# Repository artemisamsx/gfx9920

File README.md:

# Artemisa MSX - GFX9920 Graphics Card

This repository contains the KiCad project files for the GFX9920 graphics card.

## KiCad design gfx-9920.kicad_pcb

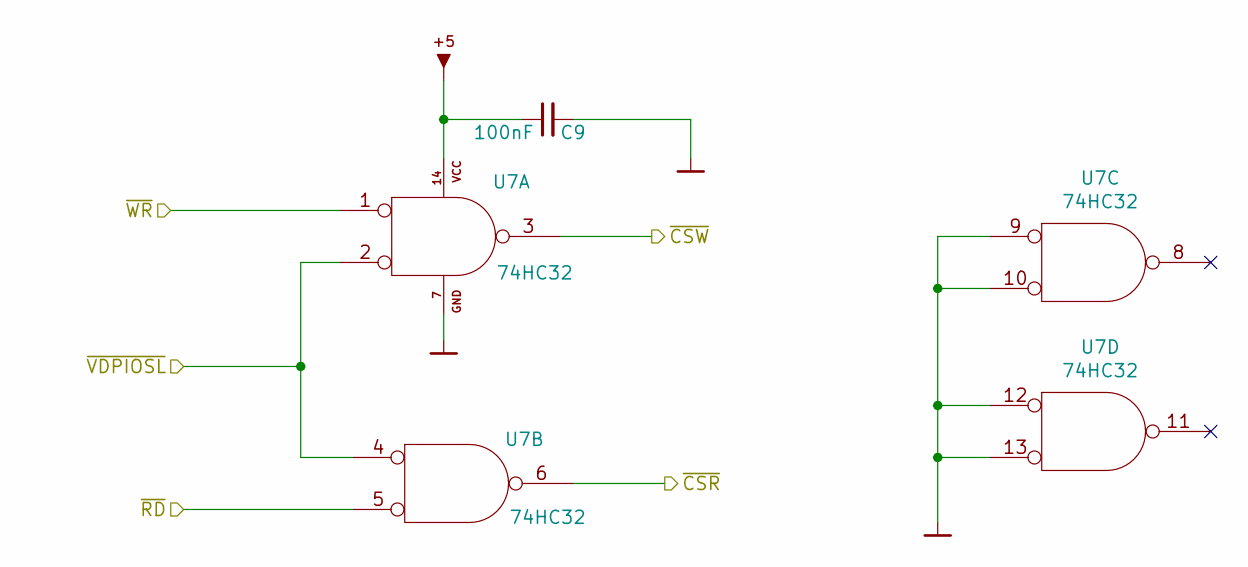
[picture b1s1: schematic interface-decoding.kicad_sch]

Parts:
C9: 100nF; Disc_capacitor
U7: 74HC32; DIP-14_300

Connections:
/Card connector & power/BUSDIR: U7.6; also elsewhere on the board
/Card connector & power/~RD: U7.5; also elsewhere on the board
/Card connector & power/~VDPIOSL: U7.2, U7.4; also elsewhere on the board
/Card connector & power/~WR: U7.1; also elsewhere on the board
/Interface Decoding Logic/~CSW: U7.3; also elsewhere on the board
GND: C9.2, U7.7 (GND), U7.9, U7.10, U7.12, U7.13; also elsewhere on the board
VCC: C9.1, U7.14 (VCC); also elsewhere on the board

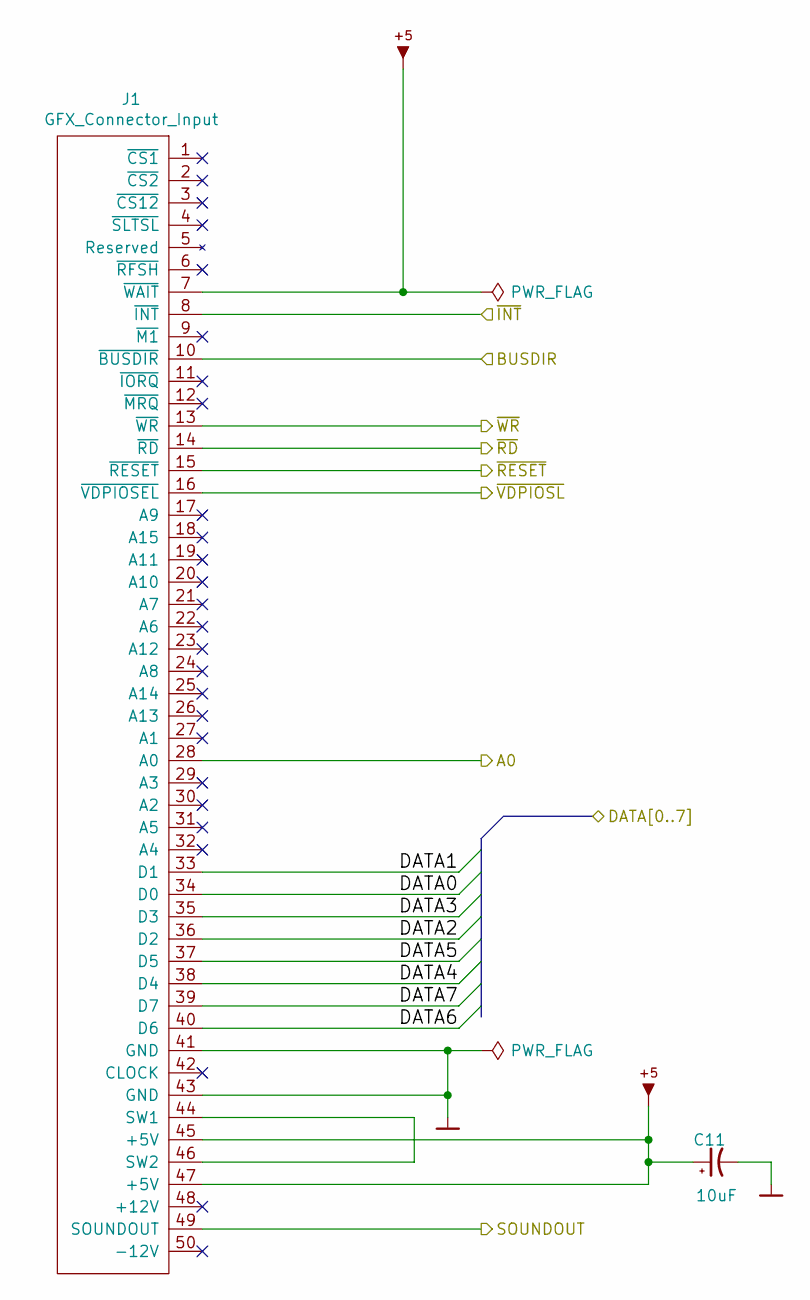
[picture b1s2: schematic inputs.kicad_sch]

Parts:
C11: 10uF; Radial_capacitor
J1: GFX_Connector_Input; GFX_conn

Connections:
/Card connector & power/A0: J1.28 (A0); also elsewhere on the board
/Card connector & power/BUSDIR: J1.10 (~BUSDIR); also elsewhere on the board
/Card connector & power/SOUNDOUT: J1.49 (SOUNDOUT); also elsewhere on the board
/Card connector & power/~INT: J1.8 (~INT); also elsewhere on the board
/Card connector & power/~RD: J1.14 (~RD); also elsewhere on the board
/Card connector & power/~RESET: J1.15 (~RESET); also elsewhere on the board
/Card connector & power/~VDPIOSL: J1.16 (~VDPIOSEL); also elsewhere on the board
/Card connector & power/~WR: J1.13 (~WR); also elsewhere on the board
/DATA0: J1.34 (D0); also elsewhere on the board
/DATA1: J1.33 (D1); also elsewhere on the board
/DATA2: J1.36 (D2); also elsewhere on the board
/DATA3: J1.35 (D3); also elsewhere on the board
/DATA4: J1.38 (D4); also elsewhere on the board
/DATA5: J1.37 (D5); also elsewhere on the board
/DATA6: J1.40 (D6); also elsewhere on the board
/DATA7: J1.39 (D7); also elsewhere on the board
GND: C11.2, J1.41 (GND), J1.43 (GND); also elsewhere on the board
unnamed: J1.44 (SW1), J1.46 (SW2)
VCC: C11.1, J1.7 (~WAIT), J1.45 (+5V), J1.47 (+5V); also elsewhere on the board

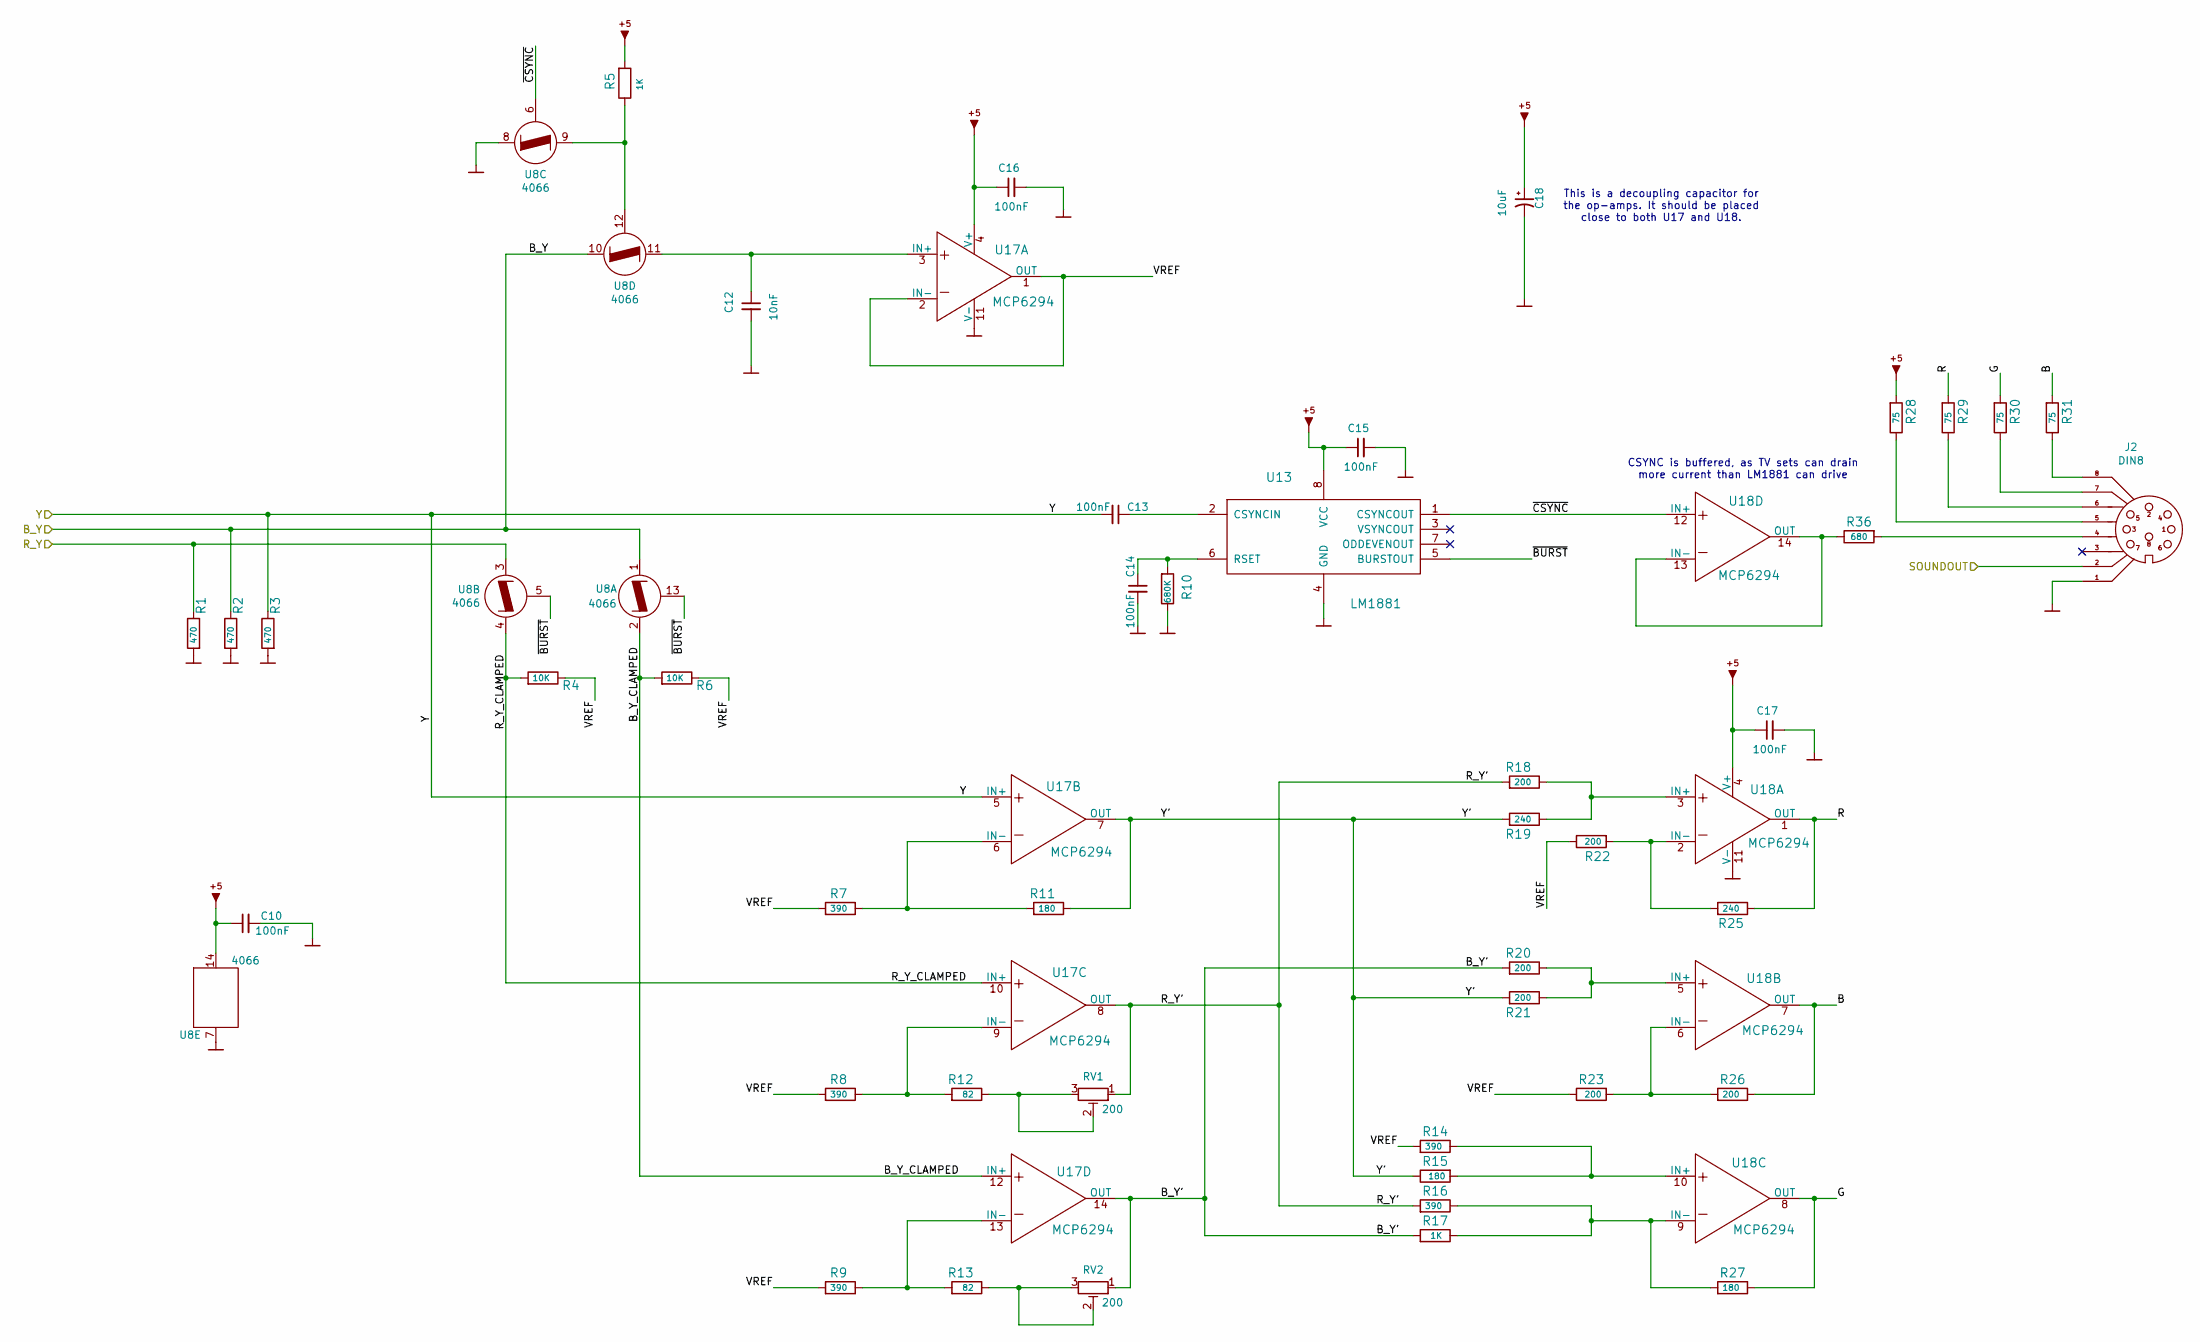
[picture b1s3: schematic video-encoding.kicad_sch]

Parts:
C10, C13, C14, C15, C16, C17: 100nF; Disc_capacitor
C12: 10nF; C_Rect_L7.0mm_W3.5mm_P2.50mm_P5.00mm
C18: 10uF; Radial_capacitor
J2: DIN8
R1, R2, R3: 470; Axial_resistor
R4, R6: 10K; Axial_resistor
R5, R17: 1K; Axial_resistor
R7, R8, R9, R14, R16: 390; Axial_resistor
R10: 680K; Axial_resistor
R11, R15, R27: 180; Axial_resistor
R12, R13: 82; Axial_resistor
R18, R20, R21, R22, R23, R26: 200; Axial_resistor
R19, R25: 240; Axial_resistor
R28, R29, R30, R31: 75; Axial_resistor
R36: 680; Axial_resistor
RV1, RV2: 200; Potentiometer_Bourns_3296W_Vertical
U8: 4066; DIP-14_300
U13: LM1881; DIP-8_300
U17, U18: MCP6294; DIP-14_300

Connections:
/Card connector & power/SOUNDOUT: J2.2; also elsewhere on the board
/Video Display Processor/R_Y: R1.1, U8.3; also elsewhere on the board
/Video Encoding/B: R26.1, R31.2, U18.7 (OUT)
/Video Encoding/B_Y: R2.1, U8.1, U8.10; also elsewhere on the board
/Video Encoding/B_Y': R17.2, R20.2, RV2.1, U17.14 (OUT)
/Video Encoding/B_Y_CLAMPED: R6.2, U8.2, U17.12 (IN+)
/Video Encoding/G: R27.1, R30.2, U18.8 (OUT)
/Video Encoding/R: R25.1, R29.2, U18.1 (OUT)
/Video Encoding/R_Y': R16.2, R18.2, RV1.1, U17.8 (OUT)
/Video Encoding/R_Y_CLAMPED: R4.2, U8.4, U17.10 (IN+)
/Video Encoding/VREF: R4.1, R6.1, R7.2, R8.2, R9.2, R14.2, R22.1, R23.1, U17.1 (OUT), U17.2 (IN-)
/Video Encoding/Y: C13.2, R3.1, U17.5 (IN+); also elsewhere on the board
/Video Encoding/Y': R11.1, R15.1, R19.2, R21.2, U17.7 (OUT)
/Video Encoding/~BURST: U8.5, U8.13, U13.5 (BURSTOUT)
/Video Encoding/~CSYNC: U8.6, U13.1 (CSYNCOUT), U18.12 (IN+)
GND: C10.2, C12.2, C14.2, C15.2, C16.2, C17.2, C18.2, J2.1, R1.2, R2.2, R3.2, R10.1, U8.7, U8.8, U13.4 (GND), U17.11 (V-), U18.11 (V-); also elsewhere on the board
unnamed: J2.4, R36.2
unnamed: J2.5, R28.1
unnamed: J2.6, R29.1
unnamed: J2.7, R30.1
unnamed: J2.8, R31.1
unnamed: R5.1, U8.9, U8.12
unnamed: R12.1, RV1.2, RV1.3
unnamed: R13.1, RV2.2, RV2.3
unnamed: C13.1, U13.2 (CSYNCIN)
unnamed: C14.1, R10.2, U13.6 (RSET)
unnamed: C12.1, U8.11, U17.3 (IN+)
unnamed: R7.1, R11.2, U17.6 (IN-)
unnamed: R8.1, R12.2, U17.9 (IN-)
unnamed: R9.1, R13.2, U17.13 (IN-)
unnamed: R18.1, R19.1, U18.3 (IN+)
unnamed: R22.2, R25.2, U18.2 (IN-)
unnamed: R20.1, R21.1, U18.5 (IN+)
unnamed: R23.2, R26.2, U18.6 (IN-)
unnamed: R14.1, R15.2, U18.10 (IN+)
unnamed: R16.1, R17.1, R27.2, U18.9 (IN-)
unnamed: R36.1, U18.13 (IN-), U18.14 (OUT)
VCC: C10.1, C15.1, C16.1, C17.1, C18.1, R5.2, R28.2, U8.14 (VCC_14), U13.8 (VCC), U17.4 (V+), U18.4 (V+); also elsewhere on the board

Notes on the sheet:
CSYNC is buffered, as TV sets can drain more current than LM1881 can drive
This is a decoupling capacitor for the op-amps. It should be placed close to both U17 and U18.

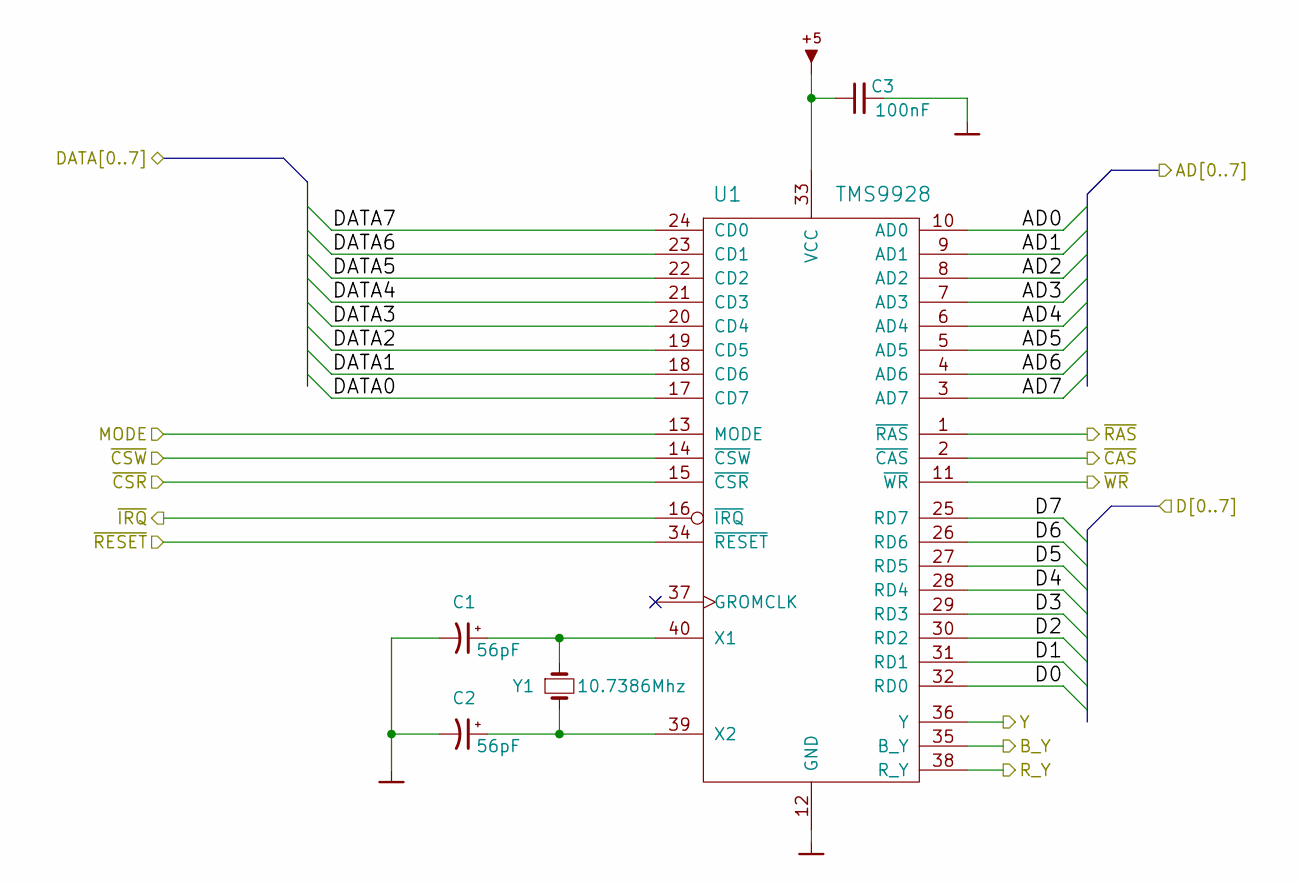
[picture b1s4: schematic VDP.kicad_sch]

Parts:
C1, C2: 56pF; Disc_capacitor
C3: 100nF; Disc_capacitor
U1: TMS9928; DIP-40_600
Y1: 10.7386Mhz; Crystal

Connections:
/AD0: U1.10 (AD0); also elsewhere on the board
/AD1: U1.9 (AD1); also elsewhere on the board
/AD2: U1.8 (AD2); also elsewhere on the board
/AD3: U1.7 (AD3); also elsewhere on the board
/AD4: U1.6 (AD4); also elsewhere on the board
/AD5: U1.5 (AD5); also elsewhere on the board
/AD6: U1.4 (AD6); also elsewhere on the board
/AD7: U1.3 (AD7); also elsewhere on the board
/Card connector & power/A0: U1.13 (MODE); also elsewhere on the board
/Card connector & power/BUSDIR: U1.15 (~CSR); also elsewhere on the board
/Card connector & power/~INT: U1.16 (~IRQ); also elsewhere on the board
/Card connector & power/~RESET: U1.34 (~RESET); also elsewhere on the board
/D0: U1.32 (RD0); also elsewhere on the board
/D1: U1.31 (RD1); also elsewhere on the board
/D2: U1.30 (RD2); also elsewhere on the board
/D3: U1.29 (RD3); also elsewhere on the board
/D4: U1.28 (RD4); also elsewhere on the board
/D5: U1.27 (RD5); also elsewhere on the board
/D6: U1.26 (RD6); also elsewhere on the board
/D7: U1.25 (RD7); also elsewhere on the board
/DATA0: U1.17 (CD7); also elsewhere on the board
/DATA1: U1.18 (CD6); also elsewhere on the board
/DATA2: U1.19 (CD5); also elsewhere on the board
/DATA3: U1.20 (CD4); also elsewhere on the board
/DATA4: U1.21 (CD3); also elsewhere on the board
/DATA5: U1.22 (CD2); also elsewhere on the board
/DATA6: U1.23 (CD1); also elsewhere on the board
/DATA7: U1.24 (CD0); also elsewhere on the board
/Interface Decoding Logic/~CSW: U1.14 (~CSW); also elsewhere on the board
/VRAM Decoding Logic/~CAS: U1.2 (~CAS); also elsewhere on the board
/VRAM Decoding Logic/~RAS: U1.1 (~RAS); also elsewhere on the board
/VRAM Decoding Logic/~WR: U1.11 (~WR); also elsewhere on the board
/Video Display Processor/R_Y: U1.38 (R_Y); also elsewhere on the board
/Video Encoding/B_Y: U1.35 (B_Y); also elsewhere on the board
/Video Encoding/Y: U1.36 (Y); also elsewhere on the board
GND: C1.2, C2.2, C3.2, U1.12 (GND); also elsewhere on the board
unnamed: C1.1, U1.40 (X1), Y1.1
unnamed: C2.1, U1.39 (X2), Y1.2
VCC: C3.1, U1.33 (VCC); also elsewhere on the board

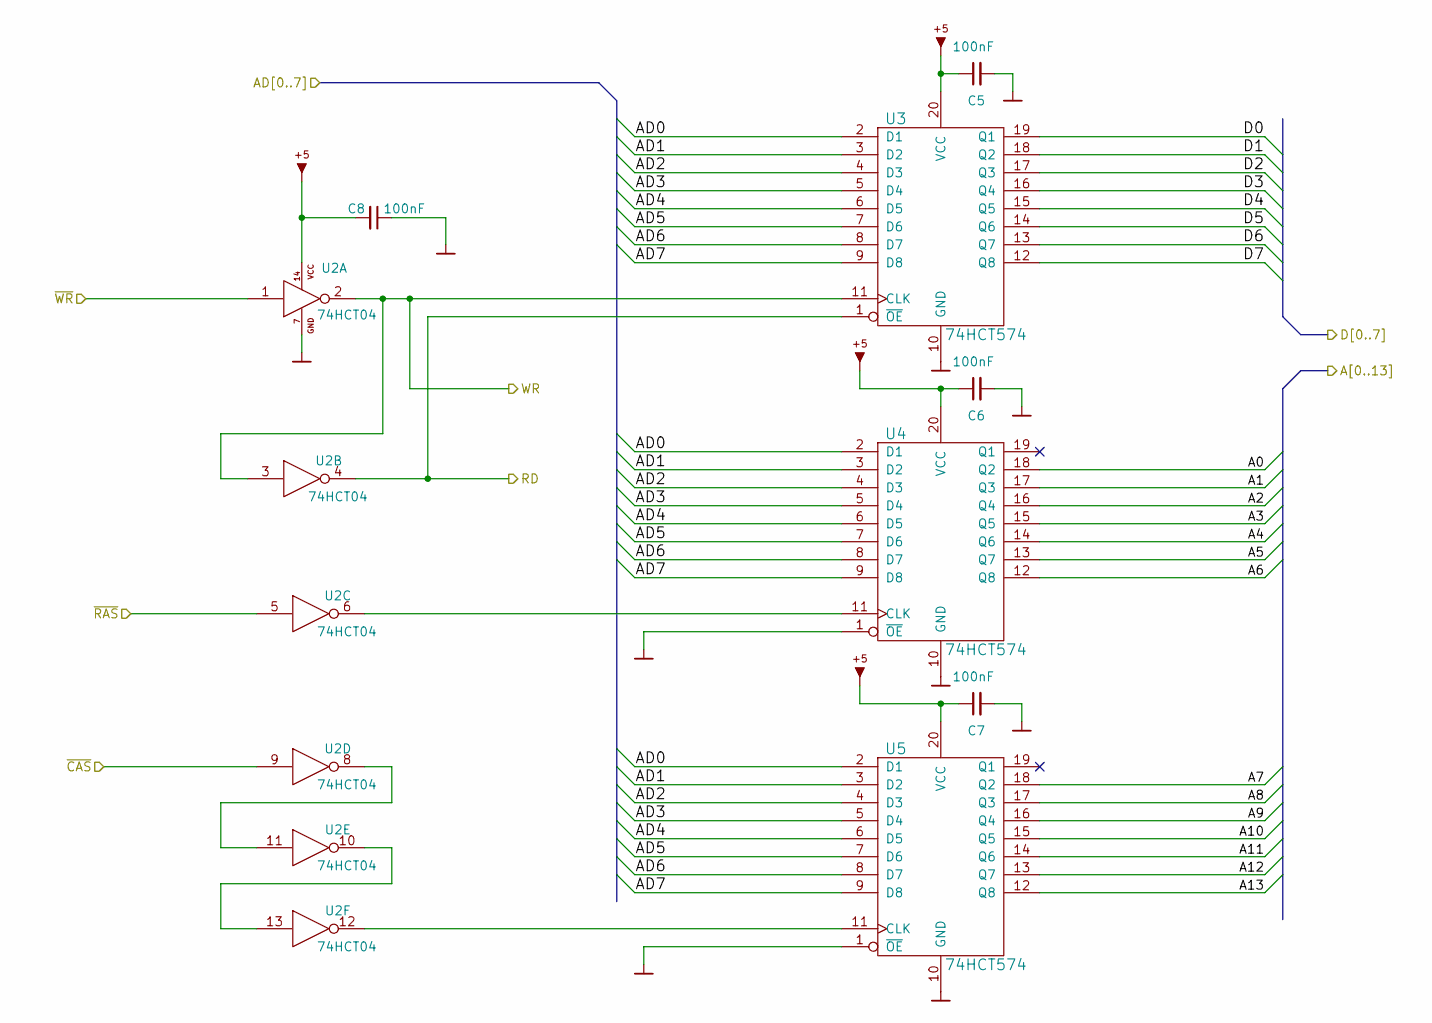
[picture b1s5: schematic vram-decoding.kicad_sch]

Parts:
C5, C6, C7, C8: 100nF; Disc_capacitor
U2: 74HCT04; DIP-14_300
U3, U4, U5: 74HCT574; DIP-20_300

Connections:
/A0: U4.18 (Q2); also elsewhere on the board
/A1: U4.17 (Q3); also elsewhere on the board
/A2: U4.16 (Q4); also elsewhere on the board
/A3: U4.15 (Q5); also elsewhere on the board
/A4: U4.14 (Q6); also elsewhere on the board
/A5: U4.13 (Q7); also elsewhere on the board
/A6: U4.12 (Q8); also elsewhere on the board
/A7: U5.18 (Q2); also elsewhere on the board
/A8: U5.17 (Q3); also elsewhere on the board
/A9: U5.16 (Q4); also elsewhere on the board
/A10: U5.15 (Q5); also elsewhere on the board
/A11: U5.14 (Q6); also elsewhere on the board
/A12: U5.13 (Q7); also elsewhere on the board
/A13: U5.12 (Q8); also elsewhere on the board
/AD0: U3.2 (D1), U4.2 (D1), U5.2 (D1); also elsewhere on the board
/AD1: U3.3 (D2), U4.3 (D2), U5.3 (D2); also elsewhere on the board
/AD2: U3.4 (D3), U4.4 (D3), U5.4 (D3); also elsewhere on the board
/AD3: U3.5 (D4), U4.5 (D4), U5.5 (D4); also elsewhere on the board
/AD4: U3.6 (D5), U4.6 (D5), U5.6 (D5); also elsewhere on the board
/AD5: U3.7 (D6), U4.7 (D6), U5.7 (D6); also elsewhere on the board
/AD6: U3.8 (D7), U4.8 (D7), U5.8 (D7); also elsewhere on the board
/AD7: U3.9 (D8), U4.9 (D8), U5.9 (D8); also elsewhere on the board
/D0: U3.19 (Q1); also elsewhere on the board
/D1: U3.18 (Q2); also elsewhere on the board
/D2: U3.17 (Q3); also elsewhere on the board
/D3: U3.16 (Q4); also elsewhere on the board
/D4: U3.15 (Q5); also elsewhere on the board
/D5: U3.14 (Q6); also elsewhere on the board
/D6: U3.13 (Q7); also elsewhere on the board
/D7: U3.12 (Q8); also elsewhere on the board
/VRAM Decoding Logic/RD: U2.4, U3.1 (~OE); also elsewhere on the board
/VRAM Decoding Logic/WR: U2.2, U2.3, U3.11 (CLK); also elsewhere on the board
/VRAM Decoding Logic/~CAS: U2.9; also elsewhere on the board
/VRAM Decoding Logic/~RAS: U2.5; also elsewhere on the board
/VRAM Decoding Logic/~WR: U2.1; also elsewhere on the board
GND: C5.2, C6.2, C7.2, C8.1, U2.7 (GND), U3.10 (GND), U4.1 (~OE), U4.10 (GND), U5.1 (~OE), U5.10 (GND); also elsewhere on the board
unnamed: U2.10, U2.13
unnamed: U2.8, U2.11
unnamed: U2.6, U4.11 (CLK)
unnamed: U2.12, U5.11 (CLK)
VCC: C5.1, C6.1, C7.1, C8.2, U2.14 (VCC), U3.20 (VCC), U4.20 (VCC), U5.20 (VCC); also elsewhere on the board

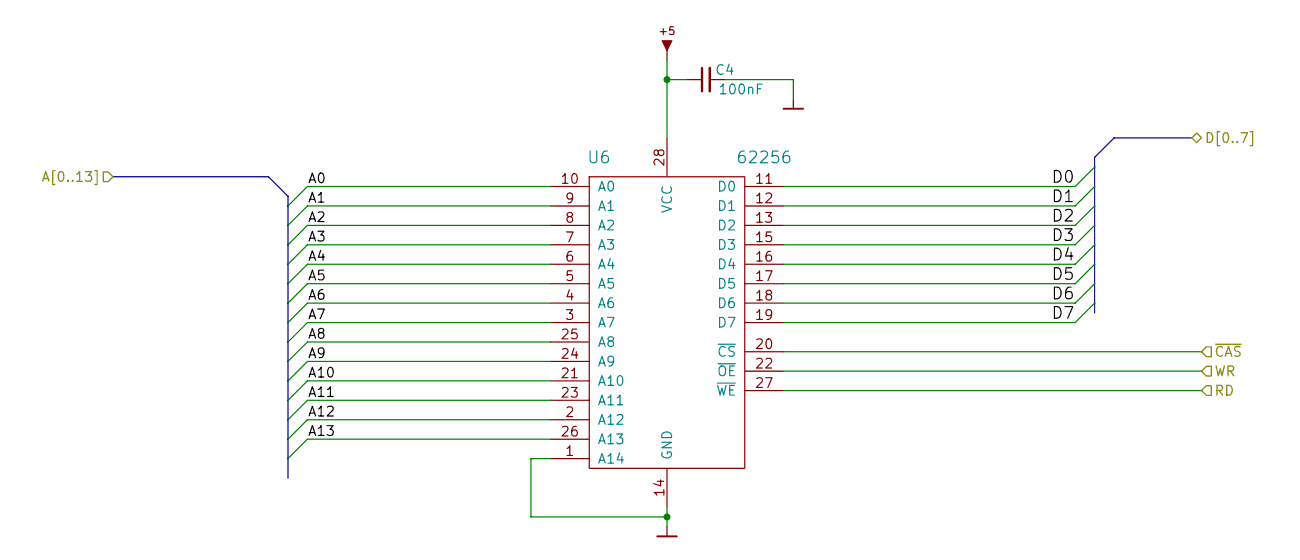
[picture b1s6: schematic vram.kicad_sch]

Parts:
C4: 100nF; Disc_capacitor
U6: 62256; DIP-28_600

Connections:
/A0: U6.10 (A0); also elsewhere on the board
/A1: U6.9 (A1); also elsewhere on the board
/A2: U6.8 (A2); also elsewhere on the board
/A3: U6.7 (A3); also elsewhere on the board
/A4: U6.6 (A4); also elsewhere on the board
/A5: U6.5 (A5); also elsewhere on the board
/A6: U6.4 (A6); also elsewhere on the board
/A7: U6.3 (A7); also elsewhere on the board
/A8: U6.25 (A8); also elsewhere on the board
/A9: U6.24 (A9); also elsewhere on the board
/A10: U6.21 (A10); also elsewhere on the board
/A11: U6.23 (A11); also elsewhere on the board
/A12: U6.2 (A12); also elsewhere on the board
/A13: U6.26 (A13); also elsewhere on the board
/D0: U6.11 (D0); also elsewhere on the board
/D1: U6.12 (D1); also elsewhere on the board
/D2: U6.13 (D2); also elsewhere on the board
/D3: U6.15 (D3); also elsewhere on the board
/D4: U6.16 (D4); also elsewhere on the board
/D5: U6.17 (D5); also elsewhere on the board
/D6: U6.18 (D6); also elsewhere on the board
/D7: U6.19 (D7); also elsewhere on the board
/VRAM Decoding Logic/RD: U6.27 (~WE); also elsewhere on the board
/VRAM Decoding Logic/WR: U6.22 (~OE); also elsewhere on the board
/VRAM Decoding Logic/~CAS: U6.20 (~CS); also elsewhere on the board
GND: C4.2, U6.1 (A14), U6.14 (GND); also elsewhere on the board
VCC: C4.1, U6.28 (VCC); also elsewhere on the board

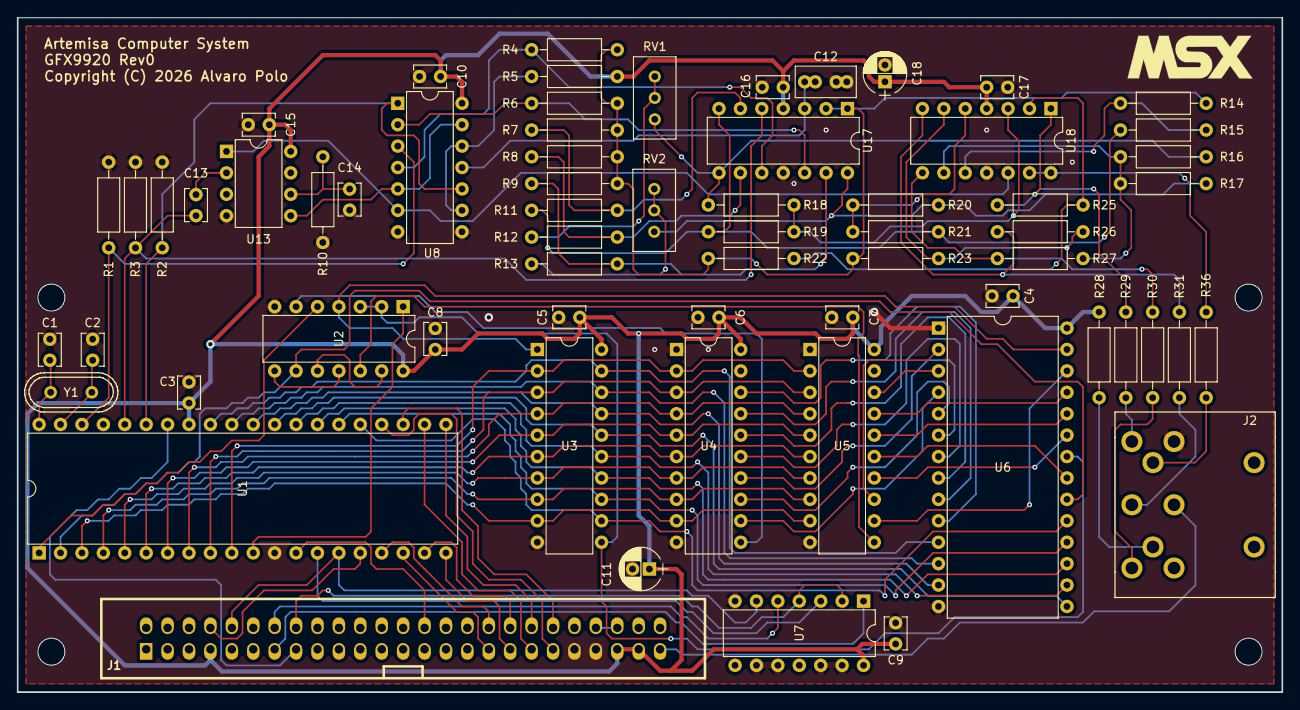
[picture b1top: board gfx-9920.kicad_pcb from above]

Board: 2 copper layers, 150.0 x 80.0 mm, 65 parts (0 on the bottom side), 96 nets.

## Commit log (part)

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2019-09-14 [gfx9920] Scaffold KiCAD project as a clone of GFX9918
2019-09-30 [WIP] GFX9920 stuff
2019-09-30 [gfx9920] Use 9928 instead of 9918
2019-09-30 [gfx9920] Introduce LM1881
2020-05-31 [GFX9920] Include working output line for /CSYNC
2020-05-31 [gfx9920] Remove extra resistors for component video lines
2020-05-31 [GFX9920] Complete the first proposal of encoder circuit
2020-06-03 [gfx9920] Move G encoding resistors to clarify
2020-06-03 [gfx9920] Fix wrong values of resistors for green encoding
2020-06-03 [gfx9920] Add a note to change the resistor from Y in G encoding
2020-06-05 [gfx9920] Fix wrong gain of blue encoding op-amp
2020-06-12 Fix the diagram to fit the successful experiments
2020-06-12 Adjust values to MAX4031 specs
2020-07-15 Add schematic circuit for power step up to 12V
2020-07-16 Add a emitter follower buffer for CSYNC
2021-03-23 Add README and LICENSE files
2021-03-23 Add kicadlibs repo as submodule
2024-11-17 Bump libs to latest version
2024-11-17 Migrate to KiCad v6
2024-11-17 Migrate to KiCad v8
2026-06-01 Migrate to KiCad v10
2026-06-01 Update to latest Artemisa kicadlibs
2026-06-02 Replace LM318 by MCP6284
2026-06-02 Remove kicadlibs as Git submodule
2026-06-02 Use spare MCP6294 as CSYNC buffer
2026-06-03 Replace unexisting 360 resistors by 390

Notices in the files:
gfx-9920.kicad_pcb:
Copyright (C) 2026 Alvaro Polo
